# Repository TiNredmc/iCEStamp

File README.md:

# iCEStamp

iCEStamp. Tiny FPGA core module based on iCE40LP1K-CM36 (iCEStamp1K) and iCE40UL1K-CM36 (iCEStampUL1K). Inspired by postage stamp, with the physical size of just 17.78 * 17.78 * 3.50 mm!

Specification
=

## iCEStamp1k
- FPGA : iCE40LP1K CM36
    - Logic Cells : 1280 cells
    - Block RAM : RAM4K * 16 (64kBits  or 8kBytes)
    - 25 I/O pins
    - Sadly no DSP block and PLL Block
    - Requires external clock/oscillator
    - x1 SPI Hardened IP
- IO Supply voltage : 2v5 to 3v3
- On board 1v2 regulator for core voltage

## iCEStampUL1K
- FPGA : iCE40UL1K CM36
    - Logic Cells : 1248 cells
    - Block RAM : RAM4K * 14 (56kBits or 7kBytes)
    - 26 I/O pins included High current sink for IR and RGB led
    - Internal 48Mhz HF oscillator and 10kHz LF oscillator
    - PLL block included 
    - x2 I2C Hardened IP
    - x1 IR TX/RX Hardened IP
    - x1 RGB PWM Hardened IP
- IO Supply voltage : 2v5 to 3v3
- On board 1v2 regulator for core voltage

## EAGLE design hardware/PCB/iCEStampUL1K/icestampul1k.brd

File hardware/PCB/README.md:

# Schematics and PCBs for iCEStamp1K and iCEStampUL1K module

Both of them are 4 layers board. Manufactured by OSHpark with the minimum trace width = 3.5 mil

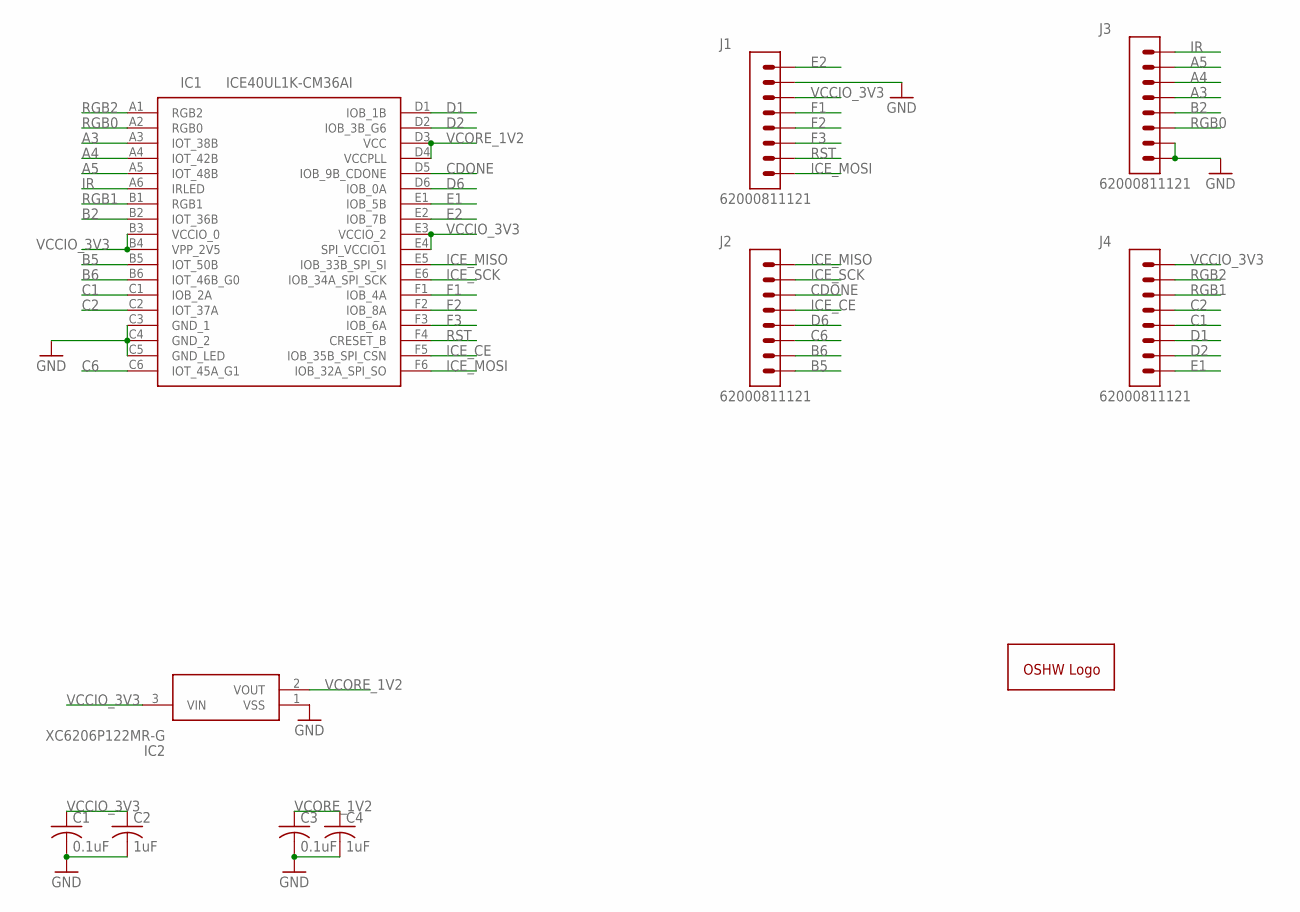
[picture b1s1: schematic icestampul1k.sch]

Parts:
C1, C3: 0.1uF; C0603
C2, C4: 1uF; C0603
GOLD_ORB_SM1: OSHWLOGOLOGO5MM; OSHW_5MM
IC1: ICE40UL1K-CM36AI; BGA36C40P6X6_250X250X91
IC2: XC6206P122MR-G; SOT95P280X130-3N
J1, J2, J3, J4: 62000811121

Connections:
A3: IC1.A3 (IOT_38B), J3.4
A4: IC1.A4 (IOT_42B), J3.3
A5: IC1.A5 (IOT_48B), J3.2
B2: IC1.B2 (IOT_36B), J3.5
B5: IC1.B5 (IOT_50B), J2.8
B6: IC1.B6 (IOT_46B_G0), J2.7
C1: IC1.C1 (IOB_2A), J4.5
C2: IC1.C2 (IOT_37A), J4.4
C6: IC1.C6 (IOT_45A_G1), J2.6
CDONE: IC1.D5 (IOB_9B_CDONE), J2.3
D1: IC1.D1 (IOB_1B), J4.6
D2: IC1.D2 (IOB_3B_G6), J4.7
D6: IC1.D6 (IOB_0A), J2.5
E1: IC1.E1 (IOB_5B), J4.8
E2: IC1.E2 (IOB_7B), J1.1
F1: IC1.F1 (IOB_4A), J1.4
F2: IC1.F2 (IOB_8A), J1.5
F3: IC1.F3 (IOB_6A), J1.6
GND: C1.2, C2.2, C3.2, C4.2, IC1.C3 (GND_1), IC1.C4 (GND_2), IC1.C5 (GND_LED), IC2.1 (VSS), J1.2, J3.7, J3.8
ICE_CE: IC1.F5 (IOB_35B_SPI_CSN), J2.4
ICE_MISO: IC1.E5 (IOB_33B_SPI_SI), J2.1
ICE_MOSI: IC1.F6 (IOB_32A_SPI_SO), J1.8
ICE_SCK: IC1.E6 (IOB_34A_SPI_SCK), J2.2
IR: IC1.A6 (IRLED), J3.1
RGB0: IC1.A2 (RGB0), J3.6
RGB1: IC1.B1 (RGB1), J4.3
RGB2: IC1.A1 (RGB2), J4.2
RST: IC1.F4 (CRESET_B), J1.7
VCCIO_3V3: C1.1, C2.1, IC1.B3 (VCCIO_0), IC1.B4 (VPP_2V5), IC1.E3 (VCCIO_2), IC1.E4 (SPI_VCCIO1), IC2.3 (VIN), J1.3, J4.1
VCORE_1V2: C3.1, C4.1, IC1.D3 (VCC), IC1.D4 (VCCPLL), IC2.2 (VOUT)

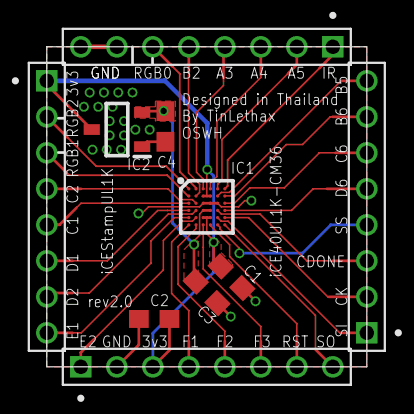
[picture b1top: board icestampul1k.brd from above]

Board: 4 copper layers, 17.8 x 17.8 mm, 11 parts (1 on the bottom side), 30 nets.

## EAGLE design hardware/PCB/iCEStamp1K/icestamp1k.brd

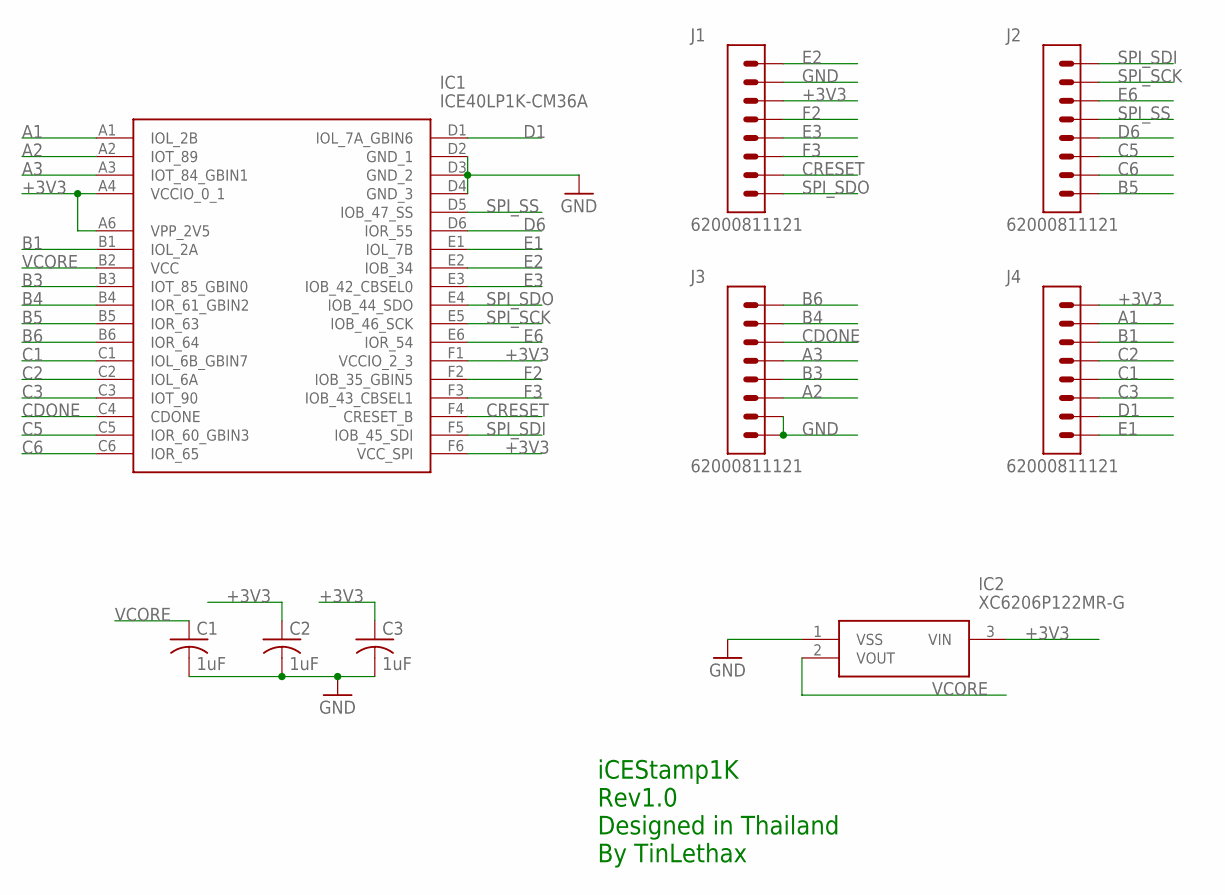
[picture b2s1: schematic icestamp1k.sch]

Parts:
C1, C2, C3: 1uF; C0603
IC1: ICE40LP1K-CM36A; BGA36C40P6X6_250X250X100
IC2: XC6206P122MR-G; SOT95P280X130-3N
J1, J2, J3, J4: 62000811121

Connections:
+3V3: C2.1, C3.1, IC1.A4 (VCCIO_0_1), IC1.A6 (VPP_2V5), IC1.F1 (VCCIO_2_3), IC1.F6 (VCC_SPI), IC2.3 (VIN), J1.3, J4.1
A1: IC1.A1 (IOL_2B), J4.2
A2: IC1.A2 (IOT_89), J3.6
A3: IC1.A3 (IOT_84_GBIN1), J3.4
B1: IC1.B1 (IOL_2A), J4.3
B3: IC1.B3 (IOT_85_GBIN0), J3.5
B4: IC1.B4 (IOR_61_GBIN2), J3.2
B5: IC1.B5 (IOR_63), J2.8
B6: IC1.B6 (IOR_64), J3.1
C1: IC1.C1 (IOL_6B_GBIN7), J4.5
C2: IC1.C2 (IOL_6A), J4.4
C3: IC1.C3 (IOT_90), J4.6
C5: IC1.C5 (IOR_60_GBIN3), J2.6
C6: IC1.C6 (IOR_65), J2.7
CDONE: IC1.C4 (CDONE), J3.3
CRESET: IC1.F4 (CRESET_B), J1.7
D1: IC1.D1 (IOL_7A_GBIN6), J4.7
D6: IC1.D6 (IOR_55), J2.5
E1: IC1.E1 (IOL_7B), J4.8
E2: IC1.E2 (IOB_34), J1.1
E3: IC1.E3 (IOB_42_CBSEL0), J1.5
E6: IC1.E6 (IOR_54), J2.3
F2: IC1.F2 (IOB_35_GBIN5), J1.4
F3: IC1.F3 (IOB_43_CBSEL1), J1.6
GND: C1.2, C2.2, C3.2, IC1.D2 (GND_1), IC1.D3 (GND_2), IC1.D4 (GND_3), IC2.1 (VSS), J1.2, J3.7, J3.8
SPI_SCK: IC1.E5 (IOB_46_SCK), J2.2
SPI_SDI: IC1.F5 (IOB_45_SDI), J2.1
SPI_SDO: IC1.E4 (IOB_44_SDO), J1.8
SPI_SS: IC1.D5 (IOB_47_SS), J2.4
VCORE: C1.1, IC1.B2 (VCC), IC2.2 (VOUT)

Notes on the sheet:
iCEStamp1K Rev1.0
Designed in Thailand By TinLethax

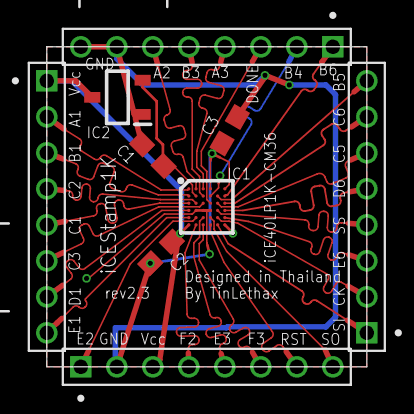
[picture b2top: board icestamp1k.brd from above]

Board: 4 copper layers, 17.8 x 17.8 mm, 9 parts (0 on the bottom side), 30 nets.

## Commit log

2022-10-24 Added iCEStamp1K and iCEStampUL1K Schematics and PCBs.
2022-10-24 Added README of PCB.
2022-10-24 Added EAGLE CAD Library for both iCEStamp1K and iCEStampUL1K modules.
2022-10-24 Added spec to README.
